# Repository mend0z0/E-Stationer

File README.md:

## Latest update

``
Working on the scheduling, hardware design, correcting diagrams, and...
``

# E-Stationer

E-Stationer is a project of consisting of two hardware parts, E-Pen and E-Paper, and 1 software parts that allow the user
to draw, write, read, and any sort of activities that you are able to do with a typical pen and paper.

## Features

- 
- 
- 

## Tech Stack

### Hardware

- **MCU:** 8bit PIC

- **Connection:** USB, UART, SPI, ADC, GPIO

- **PCB Layers:** 2Layers (None-controlled Impedance)

- **CAD:** KiCAD

### Firmware

- **OS:** State-machine

- **Programming Language:** C

- **IDE:** MPLABX IDE

### Application

- **Application:** Qt6

## WBS Chart

## Block Diagrams

## Screenshots

### Hardware

#### 3D_View

#### Assembled Hardware

### Application

## Demo

Insert gif or link to demo, it'll be my youtube channel

## LOGO

## Author

- [@Siavash Taher Parvar](https://www.linkedin.com/in/mend0z0)

## Support

[Support Link](https://github.com/sponsors/mend0z0)

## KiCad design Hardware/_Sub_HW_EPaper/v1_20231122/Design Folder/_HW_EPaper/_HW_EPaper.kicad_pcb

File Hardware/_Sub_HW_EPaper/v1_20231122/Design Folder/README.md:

# TODO list

A brief description of this todo list belongs to what project

## Tasks

- #### MUST to DO :
    - Adding 3D part to the 8-SOIC footprint for serial flash
    -
    - 
- #### Important :
    - List the works that efficient and optimized functionality of project depends on these tasks
    -
    - 
- #### General :
    - List tasks that are good to be done but the functionality of project doesn't depend on these
    -
    -

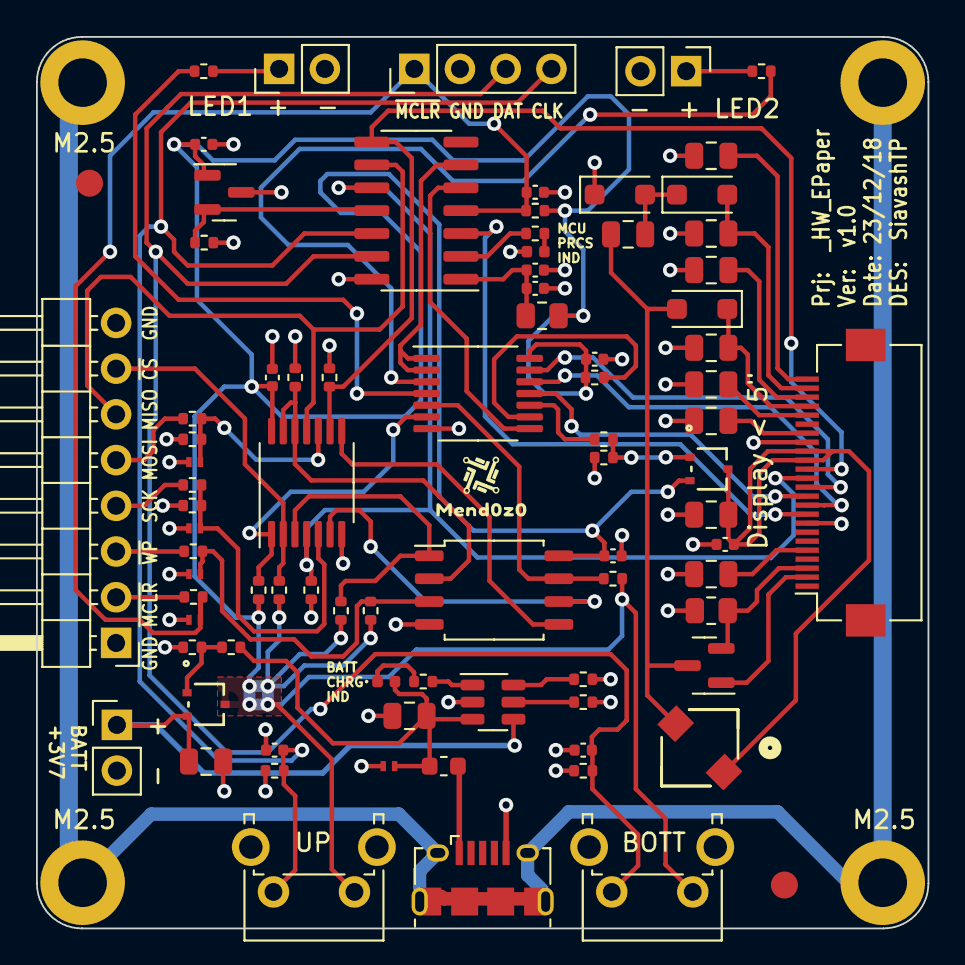
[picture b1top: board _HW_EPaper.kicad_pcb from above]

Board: 2 copper layers, 49.5 x 49.5 mm, 89 parts (0 on the bottom side), 60 nets.

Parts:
C301, C303, C703: 100nF_50V; C_0402_1005Metric
C302, C401, C501, C601, C801, C802, C901: 1uF_10V_X7R; C_0402_1005Metric
C701, C702, C704, C705, C706, C707, C708, C709, C710, C1001, C1002: 4u7F_16V; C_0805_2012Metric
D501, D502, D503, D504, D1001: TVS_6.5V_3A; CR_7PCT_L3F_TOS
D701, D702, D703: SS2040FL; D_SOD-123F
F1001: 100mA_15V_0.5R; Fuse_0603_1608Metric
FD1201, FD1202: 1.5mmX3mm; Fiducial_1.5mm_Mask3mm
GR1201: Mend0z0 Logo; LOGO_MEND0Z0
J301: HDR_4POS_VERT; PinHeader_1x04_P2.54mm_Vertical
J501: HDR_8POS_RA; PinHeader_1x08_P2.54mm_Horizontal
J701: FPC_24POS_BOTTOM_0.5P; Hirose_FH12-24S-0.5SH_1x24-1MP_P0.50mm_Horizontal
J1001: USB_microB_RA; USB_Micro-B_Amphenol_10118194_Horizontal
J1002, J1101, J1102: HDR_2POS_VERT; PinHeader_1x02_P2.54mm_Vertical
L701: 10uH_600mA; IND_CDRH3D11HPNP-100NC_SUM
LED301, LED1001: RED_2V; LED_0402_1005Metric
MH1201, MH1202, MH1203, MH1204: M2.5_DIN965; MountingHole_2.7mm_M2.5_DIN965_Pad
Q701: AS3400; SOT-23
Q702, Q1001: SSM3J117TU,LF; UFM_TOS
R301, R401, R402, R403, R501, R502, R505, R506, R507, R508, R509, R601, R703, R801, R802, R901, R1003, R1005: 10kR_1/16W_1%; R_0402_1005Metric
R302, R702, R1004: 470R_1/16W_1%; R_0402_1005Metric
R303: 1R_1/4W_1%; R_0805_2012Metric
R503, R504, R510, R511: 27R_1/16W_1%; R_0402_1005Metric
R701: 0.47R_1/8W_5%; R_0805_2012Metric
R1001, R1101, R1102: 100R_1/10W_1%; R_0402_1005Metric
R1002: 30kR_1/16W_1%; R_0402_1005Metric
SW801, SW802: SPST-NO; SW_Tactile_SPST_Angled_PTS645Vx31-2LFS
U301: PIC16F15223_8BIT; SO-14_3.9x8.65mm_P1.27mm
U401: W25Q64JVSSIQ; SOIC-8_5.275x5.275mm_P1.27mm
U501: SN74HCS32PWR; TSSOP-14_4.4x5mm_P0.65mm
U601: 74VHC164FT; TSSOP-14_4.4x5mm_P0.65mm
U901: MCP9700T-E/TT; SOT-23
U1001: RT9526AGE; SOT-23-6

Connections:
/BLOCK DIAGRAM/BATTERY CHARGER/RT_BATT: C1001.1, J1002.1, Q1001.2, U1001.4 (BATT)
/BLOCK DIAGRAM/BATTERY CHARGER/RT_CHG_SB: R1001.2, U1001.1 (CHG_SB)
/BLOCK DIAGRAM/BATTERY CHARGER/RT_IMIN: R1003.1, U1001.6 (IMIN)
/BLOCK DIAGRAM/BATTERY CHARGER/RT_ISET: R1002.1, U1001.5 (ISET)
/BLOCK DIAGRAM/BATTERY CHARGER/VBUS: C1002.1, D1001.1, F1001.2, LED1001.2, R1004.1, U1001.3 (VIN)
/BLOCK DIAGRAM/BATTERY CHARGER/V_BATT: C401.1, C501.1, C601.1, C901.1, Q702.2, Q1001.3, R301.1, R303.1, R401.1, R402.1, R403.1, R501.1, R502.1, R601.1, SW801.1, SW802.1, U401.8 (VCC), U501.14 (VCC), U601.14 (VCC), U901.1 (VDD)
/BLOCK DIAGRAM/DISPLAY DRIVER/E24_BUSY: J701.9, U301.3 (RA4)
/BLOCK DIAGRAM/DISPLAY DRIVER/E24_DC: J701.11, U601.11 (QF)
/BLOCK DIAGRAM/DISPLAY DRIVER/E24_GDR: J701.2, Q701.1
/BLOCK DIAGRAM/DISPLAY DRIVER/E24_RESE: J701.3, Q701.2, R701.1
/BLOCK DIAGRAM/DISPLAY DRIVER/E24_RST: J701.10, U601.12 (QG)
/BLOCK DIAGRAM/DISPLAY DRIVER/E24_VCOM: C709.1, J701.24
/BLOCK DIAGRAM/DISPLAY DRIVER/E24_VDD: C704.1, J701.18
/BLOCK DIAGRAM/DISPLAY DRIVER/E24_VDH: C706.1, J701.20
/BLOCK DIAGRAM/DISPLAY DRIVER/E24_VDHR: C701.1, J701.5
/BLOCK DIAGRAM/DISPLAY DRIVER/E24_VDL: C707.1, J701.22
/BLOCK DIAGRAM/DISPLAY DRIVER/E24_VGH: C705.1, D701.1, J701.21
/BLOCK DIAGRAM/DISPLAY DRIVER/E24_VGL: C710.1, D702.2, J701.23
/BLOCK DIAGRAM/DISPLAY DRIVER/E24_~CS: J701.12, U601.13 (QH)
/BLOCK DIAGRAM/DISPLAY DRIVER/PWR: R702.1, U601.10 (QE)
/BLOCK DIAGRAM/DISPLAY DRIVER/SPI_CLK: J701.13, R506.1, U301.10 (RC0), U501.4 (2A)
/BLOCK DIAGRAM/DISPLAY DRIVER/SPI_SDO: J701.14, R509.1, U301.8 (RC2), U501.9 (3A)
/BLOCK DIAGRAM/INPUT CIRCUIT/EXTERNAL_EEPROM_~WP: J501.3, R510.1
/BLOCK DIAGRAM/INPUT CIRCUIT/EXTERNAL_MCU_~MCLR: J501.2, R511.1
/BLOCK DIAGRAM/INPUT CIRCUIT/EXTERNAL_SPI_MISO: J501.6, U301.9 (RC1), U501.11 (4Y)
/BLOCK DIAGRAM/INPUT CIRCUIT/EXTERNAL_SPI_MOSI: J501.5, R504.1
/BLOCK DIAGRAM/INPUT CIRCUIT/EXTERNAL_SPI_SCK: J501.4, R503.1
/BLOCK DIAGRAM/INPUT CIRCUIT/EXTERNAL_SPI_~CS: J501.7, R501.2, U501.2 (1B)
/BLOCK DIAGRAM/INPUT CIRCUIT/MCU_SPI_~CS: R502.2, U501.1 (1A), U601.6 (QD)
/BLOCK DIAGRAM/INPUT CIRCUIT/SF_CLK: U401.6 (CLK), U501.6 (2Y)
/BLOCK DIAGRAM/INPUT CIRCUIT/SF_DI: U401.5 (DI), U501.8 (3Y)
/BLOCK DIAGRAM/INPUT CIRCUIT/SF_DO: R507.1, U401.2 (DO), U501.12 (4A), U501.13 (4B)
/BLOCK DIAGRAM/INPUT CIRCUIT/SF_~CS: R401.2, U401.1 (~CS), U501.3 (1Y)
/BLOCK DIAGRAM/INPUT CIRCUIT/SF_~WP: D503.1, R402.2, R510.2, U401.3 (~WP)
/BLOCK DIAGRAM/LED DRIVER/LED_1: R1101.1, U601.4 (QB)
/BLOCK DIAGRAM/LED DRIVER/LED_2: R1102.1, U601.3 (QA)
/BLOCK DIAGRAM/MICROCONTROLLER/IND_LED: R302.1, U301.2 (RA5)
/BLOCK DIAGRAM/MICROCONTROLLER/PIC_ICSPCLK: C802.1, J301.4, R802.1, SW802.2, U301.12 (ICSPCLK/RA1)
/BLOCK DIAGRAM/MICROCONTROLLER/PIC_ICSPDAT: C801.1, J301.3, R801.1, SW801.2, U301.13 (ICSPDAT/RA0)
/BLOCK DIAGRAM/MICROCONTROLLER/PIC_~MCLR: C301.1, D504.1, J301.1, R301.2, R511.2, U301.4 (~MCLR/RA3)
/BLOCK DIAGRAM/MICROCONTROLLER/SIPO_CLK: U301.5 (RC5), U601.8 (CK)
/BLOCK DIAGRAM/MICROCONTROLLER/SIPO_DATA: U301.6 (RC4), U601.1 (A), U601.2 (B)
/BLOCK DIAGRAM/MICROCONTROLLER/TEMP_ADC: R901.1, U301.11 (RA2), U901.2 (VOUT)
/BLOCK DIAGRAM/SERIAL FLASH/SF_~HOLD: R403.2, U401.7 (~HOLD), U601.5 (QC)
/BLOCK DIAGRAM/SHIFT REGISTER (SIPO)/74VHC164_~CLR: R601.2, U601.9 (~CLR)
Earth: J1001.6 (SH), MH1201.1, MH1202.1, MH1203.1, MH1204.1
GND: C301.2, C302.2, C303.2, C401.2, C501.2, C601.2, C701.2, C702.2, C703.2, C704.2, C705.2, C706.2, C707.2, C709.2, C710.2, C801.2, C802.2, C901.2, C1001.2, C1002.2, D501.2, D502.2, D503.2, D504.2, D703.1, D1001.2, J301.2, J501.1, J501.8, J701.8, J701.17, J1001.5 (GND), J1002.2, J1101.2, J1102.2, LED301.1, R505.2, R506.2, R507.2, R508.2, R509.2, R701.2, R703.2, R801.2, R802.2, R901.2, R1002.2, R1003.2, R1005.2, U301.14 (VSS), U401.4 (GND), U501.7 (GND), U601.7 (GND), U901.3 (GND), U1001.2 (GND)
unnamed: C702.1, C703.1, J701.15, J701.16, L701.1, Q702.3
unnamed: C708.1, D701.2, L701.2, Q701.3
unnamed: C708.2, D702.1, D703.2
unnamed: F1001.1, J1001.1 (VBUS)
unnamed: J1101.1, R1101.2
unnamed: J1102.1, R1102.2
unnamed: LED301.2, R302.2
unnamed: LED1001.1, R1001.1
unnamed: Q702.1, R702.2, R703.1
unnamed: Q1001.1, R1004.2, R1005.1
unnamed: C302.1, C303.1, R303.2, U301.1 (VDD)
unnamed: D501.1, R503.2, R505.1, U501.5 (2B)
unnamed: D502.1, R504.2, R508.1, U501.10 (3B)

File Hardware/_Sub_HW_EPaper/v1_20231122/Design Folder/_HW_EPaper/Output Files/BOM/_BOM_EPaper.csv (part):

"null","Sourced","Placed","References","Value","Footprint","Link","Description","Manufacturer","Part Number (Manufacturer)","Part Number (Vendor)","Vendor","Quantity"
1,"","","C701, C702, C704, C705, C706, C707, C708, C709, C710, C1001, C1002","4u7F_16V","C_0805_2012Metric","https://www.digikey.ca/en/products/detail/murata-electronics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","4.7 µF ±10% 16V Ceramic Capacitor X7R 0805 (2012 Metric)","Murata Electronics","GRM21BR71C475KE51L","490-14466-2-ND","Digikey",11
2,"","","C302, C401, C501, C601, C801, C802, C901","1uF_10V_X7R","C_0402_1005Metric","https://www.digikey.ca/en/products/detail/murata-electronics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","1 µF ±10% 10V Ceramic Capacitor X7R 0402 (1005 Metric)","Murata Electronics","GRM155Z71A105KE01D","490-GRM155Z71A105KE01DTR-ND","Digikey",7
3,"","","C301, C303, C703","100nF_50V","C_0402_1005Metric","https://www.digikey.ca/en/products/detail/murata-electronics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","0.1 µF ±10% 50V Ceramic Capacitor X7R 0402 (1005 Metric)","Murata Electronics","GRM155R71H104KE14J","490-13342-2-ND","Digikey",3
4,"","","R301, R401, R402, R403, R501, R502, R505, R506, R507, R508, R509, R601, R703, R801, R802, R901, R1003, R1005","10kR_1/16W_1%","R_0402_1005Metric","https://www.digikey.ca/en/products/detail/bourns-inc/CR0402-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","10 kOhms ±1% 0.063W, 1/16W Chip Resistor 0402 (1005 Metric) Thick Film","Bourns Inc.","CR0402-FX-1002GLF","CR0402-FX-1002GLFTR-ND","Digikey",18
5,"","","R503, R504, R510, R511","27R_1/16W_1%","R_0402_1005Metric","https://www.digikey.ca/en/products/detail/bourns-inc/CR0402-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","27 Ohms ±1% 0.063W, 1/16W Chip Resistor 0402 (1005 Metric) Thick Film","Bourns Inc.","CR0402-FX-27R0GLF","CR0402-FX-27R0GLFTR-ND","Digikey",4
6,"","","R302, R702, R1004","470R_1/16W_1%","R_0402_1005Metric","https://www.digikey.ca/en/products/detail/bourns-inc/CR0402-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","470 Ohms ±1% 0.063W, 1/16W Chip Resistor 0402 (1005 Metric) Thick Film","Bourns Inc.","CR0402-FX-4700GLF","CR0402-FX-4700GLFTR-ND","Digikey",3
7,"","","R1001, R1101, R1102","100R_1/10W_1%","R_0402_1005Metric","https://www.digikey.ca/en/products/detail/koa-speer-electron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","100 Ohms ±1% 0.1W, 1/10W Chip Resistor 0402 (1005 Metric) Automotive AEC-Q200, Moisture Resistant Thick Film","KOA Speer Electronics, Inc.","RK73H1ETTP1000F","2019-RK73H1ETTP1000FTR-ND","Digikey",3
8,"","","R303","1R_1/4W_1%","R_0805_2012Metric","https://www.digikey.ca/en/products/detail/stackpole-electron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","1 Ohms ±1% 0.25W, 1/4W Chip Resistor 0805 (2012 Metric) Anti-Sulfur Thin Film","Stackpole Electronics Inc","RNCP0805FTD1R00","RNCP0805FTD1R00TR-ND","Digikey",1
9,"","","R701","0.47R_1/8W_5%","R_0805_2012Metric","https://www.digikey.ca/en/products/detail/cts-resistor-produ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","470 mOhms ±5% 0.125W, 1/8W Chip Resistor 0805 (2012 Metric) Current Sense Thick Film","CTS Resistor Products","73L3R47J","73L3R47JTR-ND","Digikey",1
10,"","","R1002","30kR_1/16W_1%","R_0402_1005Metric","https://www.digikey.ca/en/products/detail/bourns-inc/CR0402-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","30 kOhms ±1% 0.063W, 1/16W Chip Resistor 0402 (1005 Metric) Thick Film","Bourns Inc.","CR0402-FX-3002GLF","CR0402-FX-3002GLFTR-ND","Digikey",1
11,"","","L701","10uH_600mA","IND_CDRH3D11HPNP-100NC_SUM","https://www.digikey.ca/en/products/detail/sumida-america-inc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","10 µH Shielded Inductor 600 mA 413mOhm Max Nonstandard","Sumida America Components Inc.","CDRH3D11HPNP-100NC","308-1966-2-ND","Digikey",1
12,"","","D501, D502, D503, D504, D1001","TVS_6.5V_3A","CR_7PCT_L3F_TOS","https://www.digikey.ca/en/products/detail/good-ark-semicondu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","20.5V Clamp 3A (8/20µs) Ipp Tvs Diode Surface Mount SOD-882","Good-Ark Semiconductor","GSEWT5B003","4786-GSEWT5B003TR-ND","Digikey",5
13,"","","D701, D702, D703","SS2040FL","D_SOD-123F","https://www.digikey.ca/en/products/detail/panjit-internation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","Diode 40 V 2A Surface Mount SOD-123FL","Panjit International Inc.","SS2040FL_R1_00001","3757-SS2040FL_R1_00001TR-ND","Digikey",3
14,"","","U301","PIC16F15223_8BIT","SO-14_3.9x8.65mm_P1.27mm","https://www.digikey.ca/en/products/detail/microchip-technolo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","PIC PIC® 16F, Functional Safety (FuSa) Microcontroller IC 8-Bit 32MHz 3.5KB (2K x 14) FLASH 14-SOIC","Microchip Technology","PIC16F15223-E/SL","150-PIC16F15223-E/SL-ND","Digikey",1
15,"","","U401","W25Q64JVSSIQ","SOIC-8_5.275x5.275mm_P1.27mm","https://www.digikey.ca/en/products/detail/winbond-electronic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","FLASH - NOR Memory IC 64Mbit SPI - Quad I/O 133 MHz 8-SOIC","Winbond Electronics","W25Q64JVSSIQ","W25Q64JVSSIQ-ND","Digikey",1
16,"","","U501","SN74HCS32PWR","TSSOP-14_4.4x5mm_P0.65mm","https://www.digikey.ca/en/products/detail/texas-instruments/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","OR Gate IC 4 Channel Schmitt Trigger Input 14-TSSOP","Texas Instruments","SN74HCS32PWR","296-SN74HCS32PWRTR-ND","Digikey",1
17,"","","U601","74VHC164FT","TSSOP-14_4.4x5mm_P0.65mm","https://www.digikey.ca/en/products/detail/toshiba-semiconduc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","Shift Shift Register 1 Element 8 Bit 14-TSSOP","Toshiba Semiconductor and Storage","74VHC164FT","264-74VHC164FTTR-ND","Digikey",1
18,"","","U901","MCP9700T-E/TT","SOT-23","https://www.digikey.ca/en/products/detail/microchip-technolo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","Temperature Sensor Analog, Local -40°C ~ 125°C 10mV/°C SOT-23-3","Microchip Technology","MCP9700T-E/TT","MCP9700T-E/TTTR-ND","Digikey",1
19,"","","U1001","RT9526AGE","SOT-23-6","https://www.digikey.ca/en/products/detail/richtek-usa-inc/RT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","Charger IC Lithium Ion SOT-23-6","Richtek USA Inc.","RT9526AGE","1028-1359-2-ND","Digikey",1
20,"","","F1001","100mA_15V_0.5R","Fuse_0603_1608Metric","https://www.digikey.ca/en/products/detail/eaton-electronics-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","PTC Resettable Fuse 15V 100 mA Ih Surface Mount 0603 (1608 Metric), Concave","Eaton - Electronics Division","PTS060315V010","283-PTS060315V010TR-ND","Digikey",1
21,"","","SW801, SW802","SPST-NO","SW_Tactile_SPST_Angled_PTS645Vx31-2LFS","https://www.digikey.ca/en/products/detail/c-k/PTS645VH31-2-L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","Tactile Switch SPST-NO Side Actuated Through Hole, Right Angle","C&K","PTS645VH31-2 LFS","CKN9118-ND","Digikey",2
22,"","","LED301, LED1001","RED_2V","LED_0402_1005Metric","https://www.digikey.ca/en/products/detail/harvatek-corporati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","Red 624nm LED Indication - Discrete 2V 0402 (1005 Metric)","Harvatek Corporation","B2841USD-20D001014U1930","3147-B2841USD-20D001014U1930TR-ND","Digikey",2
23,"","","Q702, Q1001","SSM3J117TU,LF","UFM_TOS","https://www.digikey.ca/en/products/detail/toshiba-semiconduc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","P-Channel 30 V 2A (Ta) 500mW (Ta) Surface Mount UFM","Toshiba Semiconductor and Storage","SSM3J117TU,LF","SSM3J117TULFTR-ND","Digikey",2
24,"","","Q701","AS3400","SOT-23","https://www.digikey.ca/en/products/detail/anbon-semiconducto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","N-Channel 30 V 5.6A (Ta) 1.2W (Ta) Surface Mount SOT-23","ANBON SEMICONDUCTOR (INT'L) LIMITED","AS3400","4530-AS3400TR-ND","Digikey",1
25,"","","J1002, J1101, J1102","HDR_2POS_VERT","PinHeader_1x02_P2.54mm_Vertical","https://www.digikey.ca/en/products/detail/adam-tech/PH1-02-U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","Connector Header Through Hole 2 position 0.100"" (2.54mm)","Adam Tech","PH1-02-UA","2057-PH1-02-UA-ND","Digikey",3
26,"","","J301","HDR_4POS_VERT","PinHeader_1x04_P2.54mm_Vertical","https://www.digikey.ca/en/products/detail/adam-tech/PH1-04-U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","Connector Header Through Hole 4 position 0.100"" (2.54mm)","Adam Tech","PH1-04-UA","2057-PH1-04-UA-ND","Digikey",1
27,"","","J501","HDR_8POS_RA","PinHeader_1x08_P2.54mm_Horizontal","https://www.digikey.ca/en/products/detail/adam-tech/PH1RB-08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","Connector Header Through Hole, Right Angle 8 position 0.100"" (2.54mm)","Adam Tech","PH1RB-08-UA","2057-PH1RB-08-UA-ND","Digikey",1
28,"","","J701","FPC_24POS_BOTTOM_0.5P","Hirose_FH12-24S-0.5SH_1x24-1MP_P0.50mm_Horizontal","https://www.digikey.ca/en/products/detail/cvilux-usa/CF35242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","24 Position FFC, FPC Connector Contacts, Bottom 0.020"" (0.50mm) Surface Mount, Right Angle","Cvilux USA","CF35242D0RD-NH","2987-CF35242D0RD-NHTR-ND","Digikey",1
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
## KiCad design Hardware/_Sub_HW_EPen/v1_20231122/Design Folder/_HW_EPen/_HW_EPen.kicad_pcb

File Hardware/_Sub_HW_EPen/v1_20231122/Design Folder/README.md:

# TODO list

This todo list belongs to _SUB_HW_EPen, the hardware part of EPen sub project. 

## Tasks

- #### MUST to DO :
    - Writing the LED indicator status once it's been determined how it should blink based on different situation.
    - Adding proper screw component and link in mechanical page
    - Adding a good enclosure 
	- Adding the PCB and it's size to mechanical page
	- Adding 3D model for USB footprint (P/N: 10118194-0001LF) 
- #### Important :
    - List the works that efficient and optimized functionality of project depends on these tasks
    -
    - 
- #### General :
    - List tasks that are good to be done but the functionality of project doesn't depend on these
    -
    -

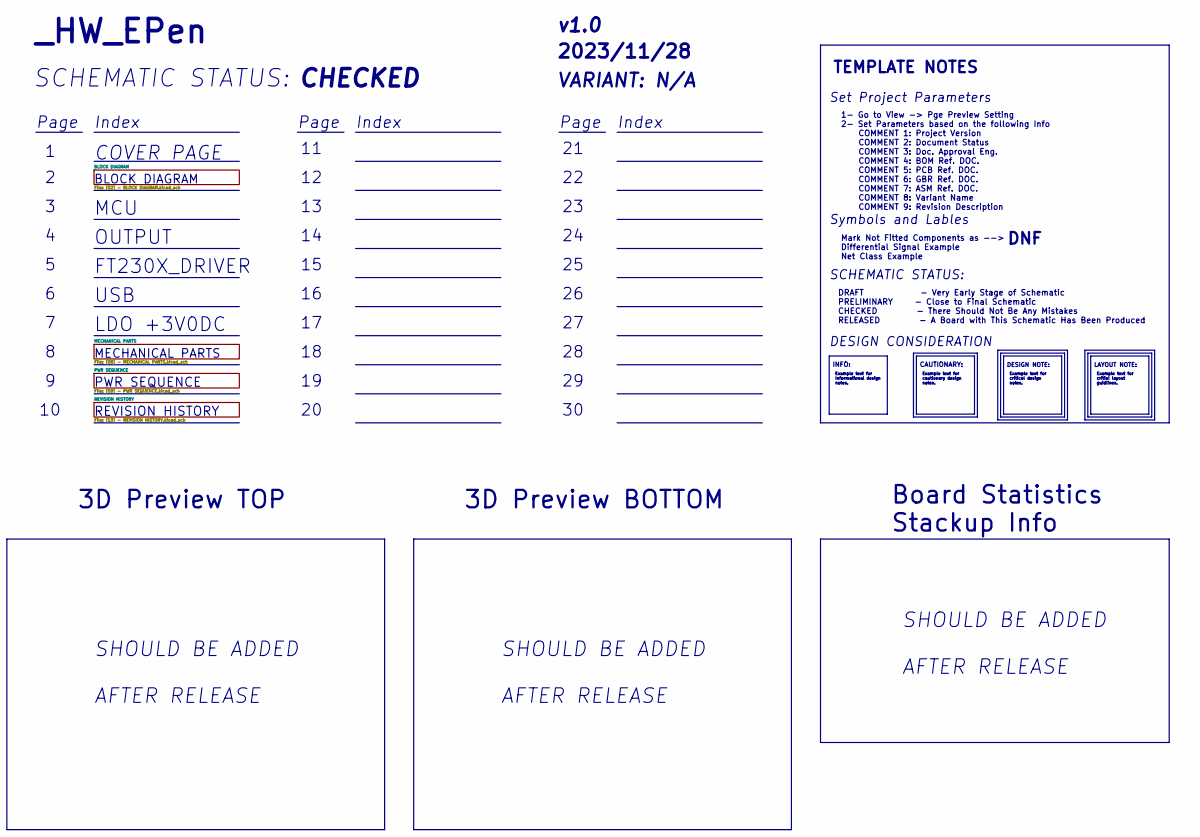
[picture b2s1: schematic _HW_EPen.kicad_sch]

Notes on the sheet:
Set Project Parameters
SHOULD BE ADDED AFTER RELEASE
MECHANICAL PARTS
Index
SCHEMATIC STATUS:
SCHEMATIC STATUS:
Page
DESIGN CONSIDERATION
USB
Example text for Informational design notes.
${COMMENT2}
${REVISION}
VARIANT: ${COMMENT8}
1- Go to View -> Pge Preview Setting 2- Set Parameters based on the following Info COMMENT 1: Project Version COMMENT 2: Document Status COMMENT 3: Doc. Approval Eng. COMMENT 4: BOM Ref. DOC. COMMENT 5: PCB Ref. DOC. COMMENT 6: GBR Ref. DOC. COMMENT 7: ASM Ref. DOC. COMMENT 8: Variant Name COMMENT 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
COVER PAGE
OUTPUT
Mark Not Fitted Components as --> Differential Signal Example Net Class Example
Board Statistics Stackup Info
TEMPLATE NOTES
${ISSUE_DATE}
Example text for critial layout guidlines.
MCU
INFO:
${TITLE}
DESIGN NOTE:
Example text for critical design notes.
3D Preview TOP
PWR SEQUENCE
3D Preview BOTTOM
Example text for cautionary design notes.
CAUTIONARY:
Symbols and Lables
DNF
LDO +3V0DC
REVISION HISTORY
FT230X_DRIVER
BLOCK DIAGRAM
LAYOUT NOTE:
DRAFT - Very Early Stage of Schematic PRELIMINARY - Close to Final Schematic CHECKED - There Should Not Be Any Mistakes RELEASED - A Board with This Schematic Has Been Produced

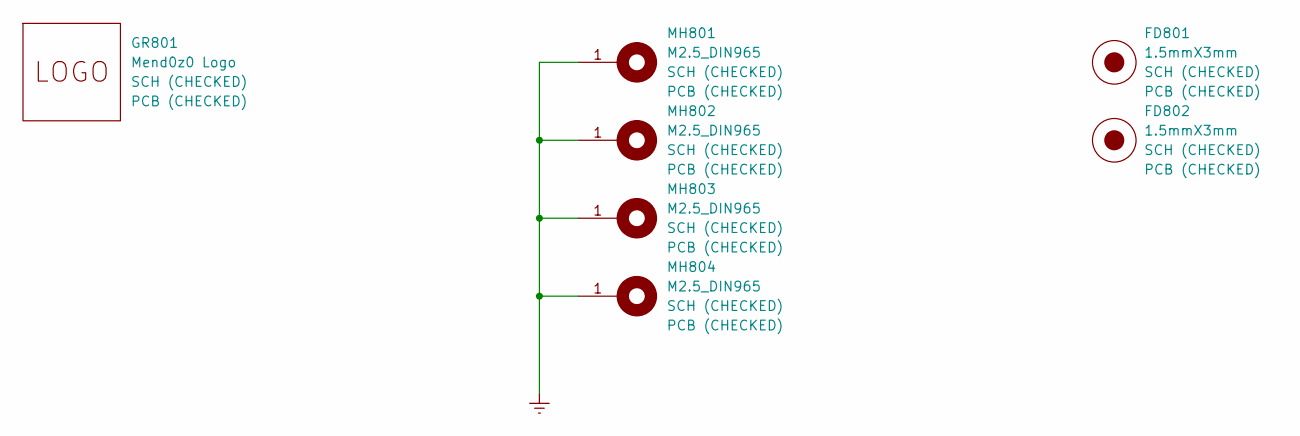
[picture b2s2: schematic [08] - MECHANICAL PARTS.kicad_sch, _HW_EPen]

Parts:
FD801, FD802: 1.5mmX3mm; Fiducial_1.5mm_Mask3mm
GR801: Mend0z0 Logo; LOGO_MEND0Z0
MH801, MH802, MH803, MH804: M2.5_DIN965; MountingHole_2.7mm_M2.5_DIN965_Pad

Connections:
Earth: MH801.1, MH802.1, MH803.1, MH804.1; also elsewhere on the board

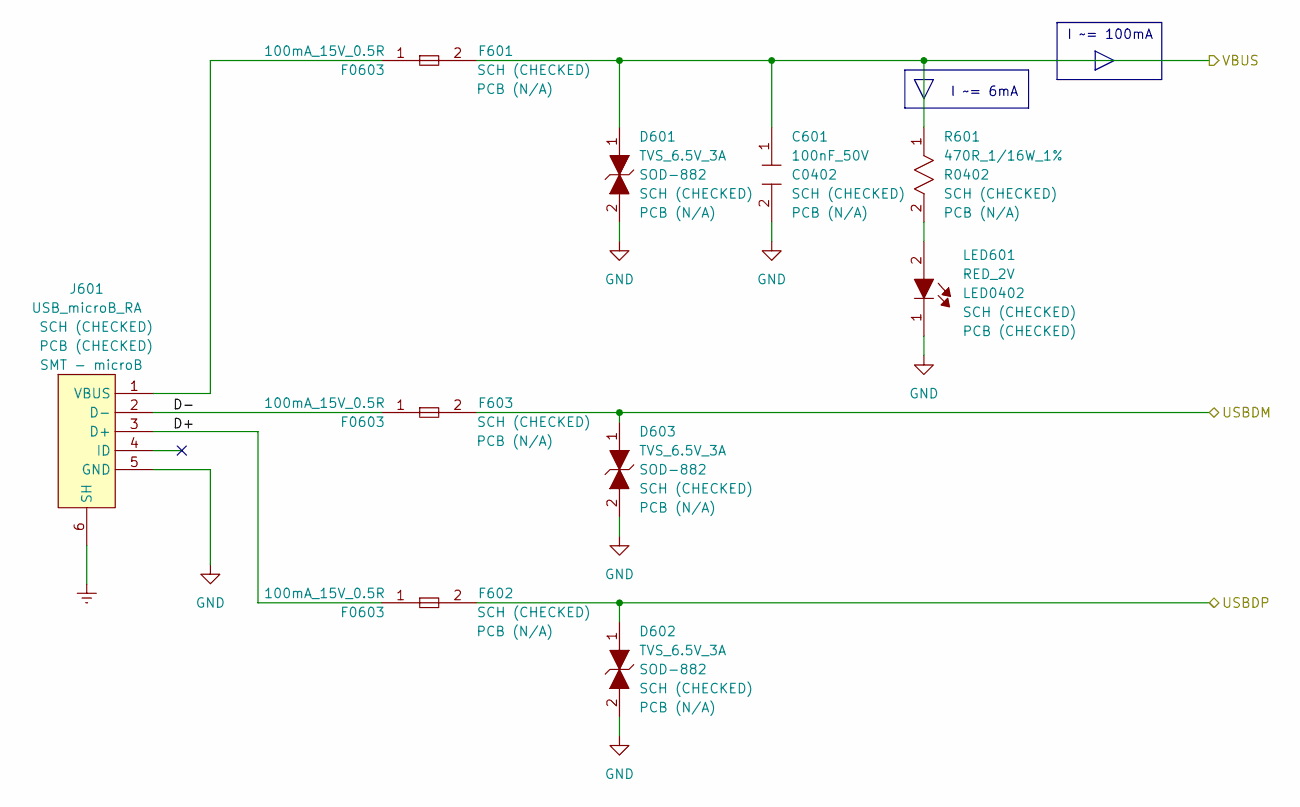
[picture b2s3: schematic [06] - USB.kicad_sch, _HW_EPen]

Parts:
C601: 100nF_50V; C_0402_1005Metric; Part Number (Manufactur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 GRM155R71H104KE14J
D601, D602, D603: TVS_6.5V_3A; CR_7PCT_L3F_TOS; Part Number (Vendor) 4786-GSEWT5B003TR-ND
F601, F602, F603: 100mA_15V_0.5R; Fuse_0603_1608Metric; Part Number (Vendor) 283-PTS060315V010TR-ND
J601: USB_microB_RA; USB_Micro-B_Amphenol_10118194_Horizontal; Part Number (Vendor) 609-4618-2-ND
LED601: RED_2V; LED_0402_1005Metric; Part Number (Vendor) 3147-B2841USD-20D001014U1930TR-ND
R601: 470R_1/16W_1%; R_0402_1005Metric; Part Number (Vendor) CR0402-FX-4700GLFTR-ND

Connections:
/BLOCK DIAGRAM/FT230X_DRIVER/USBDM: D603.1, F603.2; also elsewhere on the board
/BLOCK DIAGRAM/FT230X_DRIVER/USBDP: D602.1, F602.2; also elsewhere on the board
/BLOCK DIAGRAM/LDO +3V0DC/+5VDC: C601.1, D601.1, F601.2, R601.1; also elsewhere on the board
/BLOCK DIAGRAM/USB/D+: F602.1, J601.3 (D+)
/BLOCK DIAGRAM/USB/D-: F603.1, J601.2 (D-)
Earth: J601.6 (SH); also elsewhere on the board
GND: C601.2, D601.2, D602.2, D603.2, J601.5 (GND), LED601.1; also elsewhere on the board
unnamed: F601.1, J601.1 (VBUS)
unnamed: LED601.2, R601.2

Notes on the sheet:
I ~= 100mA
I ~= 6mA

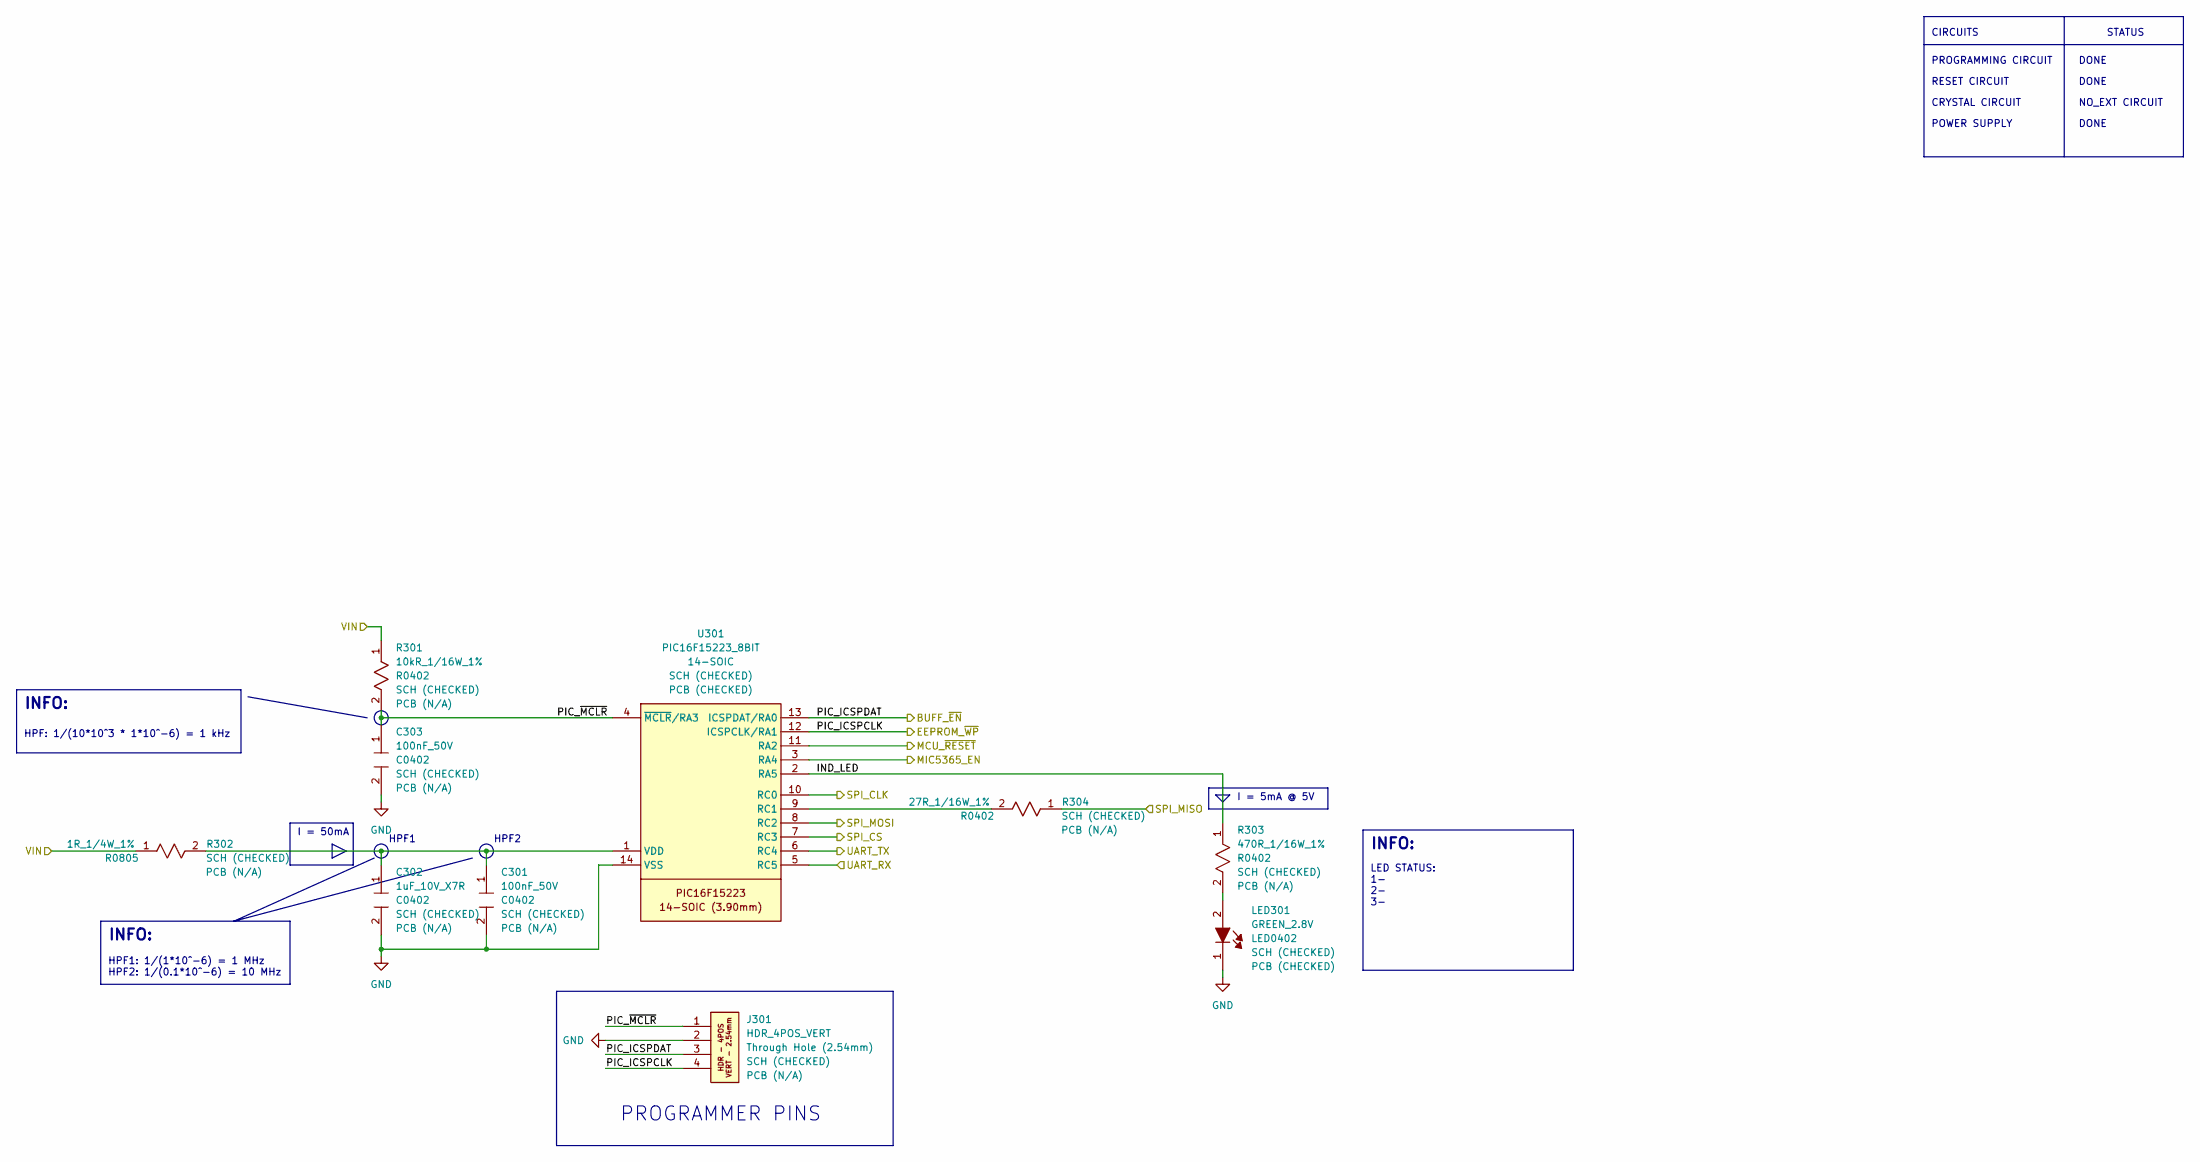
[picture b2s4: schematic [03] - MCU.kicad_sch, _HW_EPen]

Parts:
C301, C303: 100nF_50V; C_0402_1005Metric; Part Number (Manufactur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 GRM155R71H104KE14J
C302: 1uF_10V_X7R; C_0402_1005Metric; Part Number (Vendor) 490-GRM155Z71A105KE01DTR-ND
J301: HDR_4POS_VERT; PinHeader_1x04_P2.54mm_Vertical; Part Number (Vendor) 2057-PH1-04-UA-ND
LED301: GREEN_2.8V; LED_0402_1005Metric; Part Number (Vendor) 3147-B2841NG--05D000514U1930TR-ND
R301: 10kR_1/16W_1%; R_0402_1005Metric; Part Number (Vendor) CR0402-FX-1002GLFTR-ND
R302: 1R_1/4W_1%; R_0805_2012Metric; Part Number (Vendor) RNCP0805FTD1R00TR-ND
R303: 470R_1/16W_1%; R_0402_1005Metric; Part Number (Vendor) CR0402-FX-4700GLFTR-ND
R304: 27R_1/16W_1%; R_0402_1005Metric; Part Number (Vendor) CR0402-FX-27R0GLFTR-ND
U301: PIC16F15223_8BIT; SO-14_3.9x8.65mm_P1.27mm; Part Number (Vendor) 150-PIC16F15223-E/SL-ND

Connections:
/BLOCK DIAGRAM/FT230X_DRIVER/UART_RX: U301.6 (RC4); also elsewhere on the board
/BLOCK DIAGRAM/FT230X_DRIVER/UART_TX: U301.5 (RC5); also elsewhere on the board
/BLOCK DIAGRAM/LDO +3V0DC/+5VDC: R301.1, R302.1; also elsewhere on the board
/BLOCK DIAGRAM/LDO +3V0DC/MIC5365_PIN_EN: U301.3 (RA4); also elsewhere on the board
/BLOCK DIAGRAM/MCU/IND_LED: R303.1, U301.2 (RA5)
/BLOCK DIAGRAM/MCU/MCU_~RESET: U301.11 (RA2); also elsewhere on the board
/BLOCK DIAGRAM/MCU/PIC_ICSPCLK: J301.4, U301.12 (ICSPCLK/RA1); also elsewhere on the board
/BLOCK DIAGRAM/MCU/PIC_ICSPDAT: J301.3, U301.13 (ICSPDAT/RA0); also elsewhere on the board
/BLOCK DIAGRAM/MCU/PIC_~MCLR: C303.1, J301.1, R301.2, U301.4 (~MCLR/RA3)
/BLOCK DIAGRAM/MCU/SPI_CLK: U301.10 (RC0); also elsewhere on the board
/BLOCK DIAGRAM/MCU/SPI_CS: U301.7 (RC3); also elsewhere on the board
/BLOCK DIAGRAM/MCU/SPI_MISO: R304.1; also elsewhere on the board
/BLOCK DIAGRAM/MCU/SPI_MOSI: U301.8 (RC2); also elsewhere on the board
GND: C301.2, C302.2, C303.2, J301.2, LED301.1, U301.14 (VSS); also elsewhere on the board
unnamed: LED301.2, R303.2
unnamed: R304.2, U301.9 (RC1)
unnamed: C301.1, C302.1, R302.2, U301.1 (VDD)

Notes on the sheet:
HPF: 1/(10*10^3 * 1*10^-6) = 1 kHz
INFO:
I = 50mA
DONE
I = 5mA @ 5V
CRYSTAL CIRCUIT
HPF2
PROGRAMMER PINS
STATUS
LED STATUS: 1- 2- 3-
HPF1
POWER SUPPLY
NO_EXT CIRCUIT
HPF1: 1/(1*10^-6) = 1 MHz HPF2: 1/(0.1*10^-6) = 10 MHz
PROGRAMMING CIRCUIT
CIRCUITS
RESET CIRCUIT

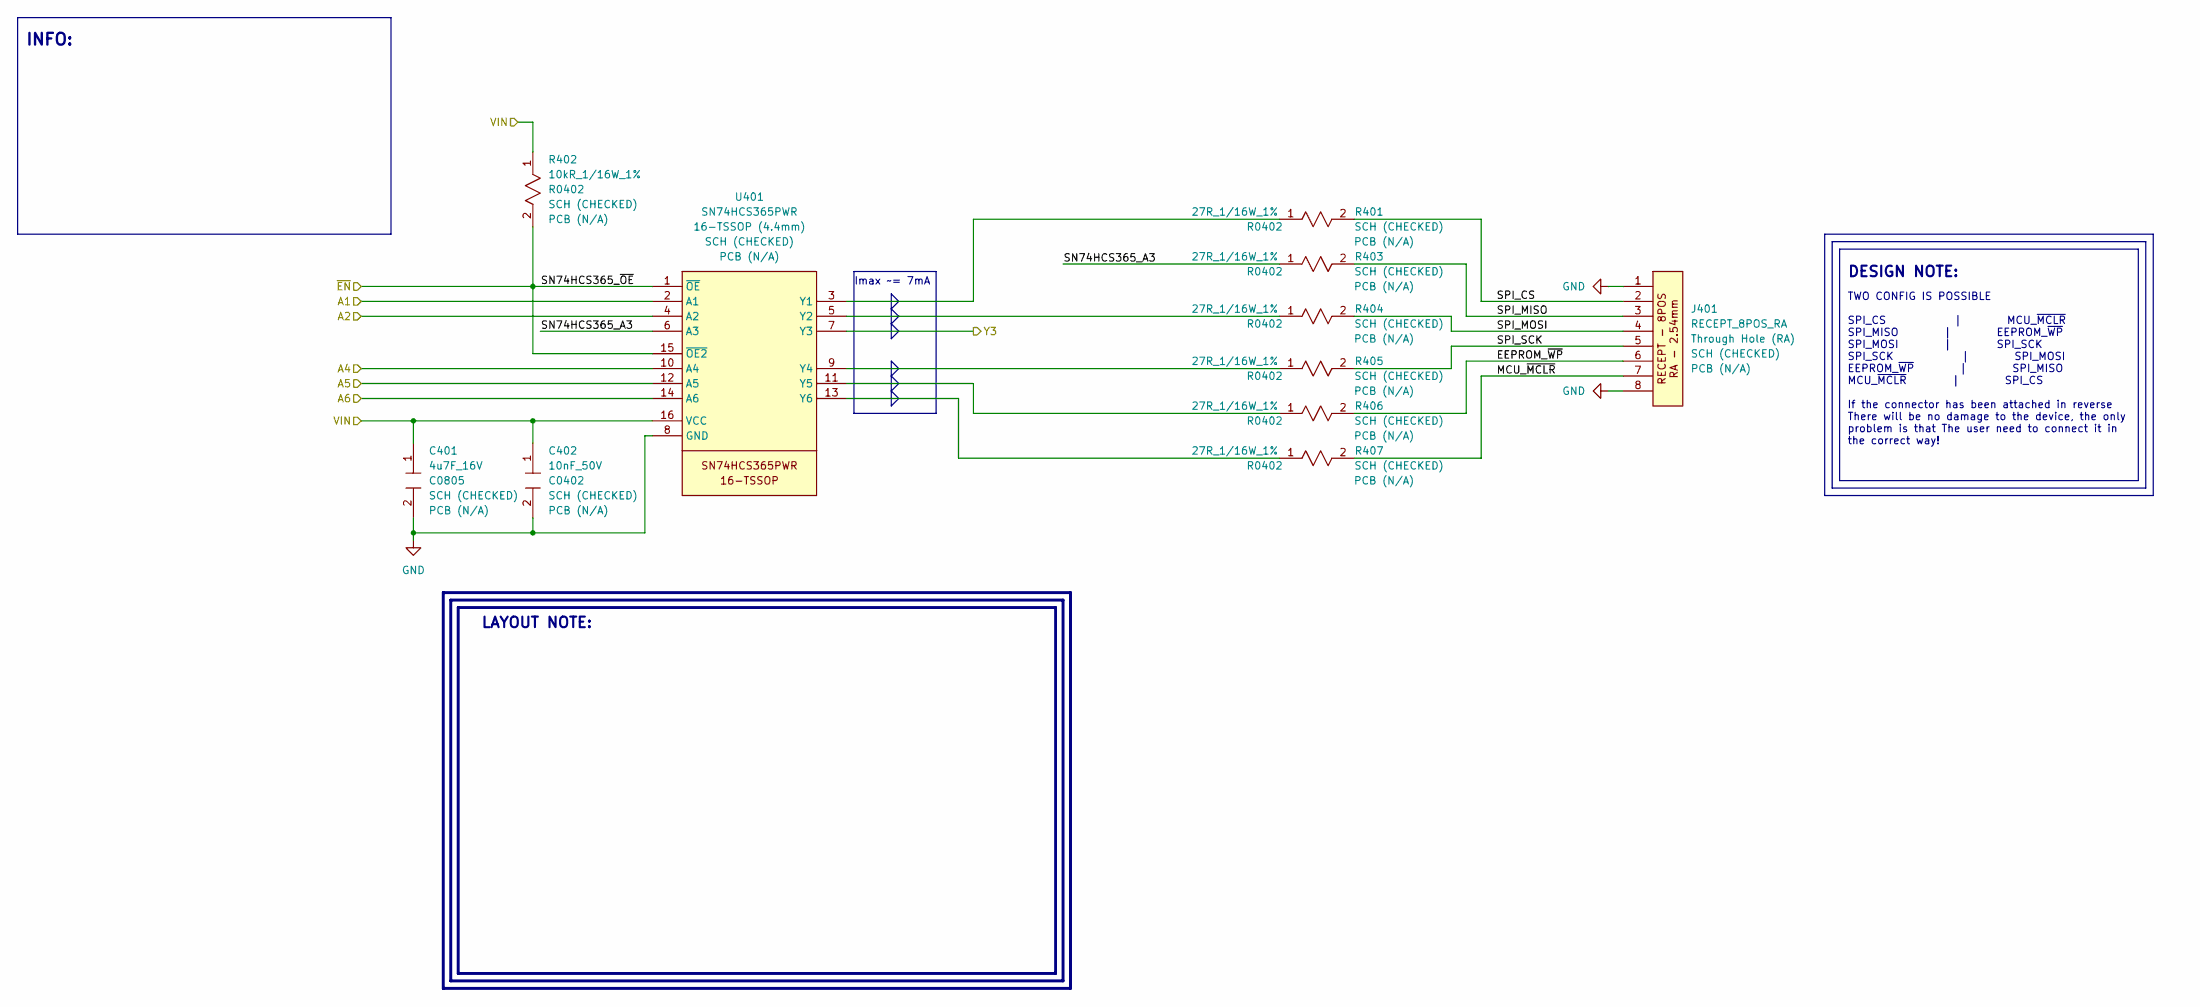
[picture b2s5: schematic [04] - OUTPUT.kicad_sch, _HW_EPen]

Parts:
C401: 4u7F_16V; C_0805_2012Metric; Part Number (Vendor) 490-14466-2-ND
C402: 10nF_50V; C_0402_1005Metric; Part Number (Vendor) 1276-1028-2-ND
J401: RECEPT_8POS_RA; PinSocket_1x08_P2.54mm_Horizontal; Part Number (Vendor) SAM1195-08-ND
R401, R403, R404, R405, R406, R407: 27R_1/16W_1%; R_0402_1005Metric; Part Number (Vendor) CR0402-FX-27R0GLFTR-ND
R402: 10kR_1/16W_1%; R_0402_1005Metric; Part Number (Vendor) CR0402-FX-1002GLFTR-ND
U401: SN74HCS365PWR; TSSOP-16_4.4x5mm_P0.65mm; Part Number (Vendor) 296-SN74HCS365PWRTR-ND

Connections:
/BLOCK DIAGRAM/LDO +3V0DC/+3VDC: C401.1, C402.1, R402.1, U401.16 (VCC); also elsewhere on the board
/BLOCK DIAGRAM/MCU/MCU_~RESET: U401.14 (A6); also elsewhere on the board
/BLOCK DIAGRAM/MCU/PIC_ICSPCLK: U401.12 (A5); also elsewhere on the board
/BLOCK DIAGRAM/MCU/PIC_ICSPDAT: R402.2, U401.1 (~OE), U401.15 (~OE2); also elsewhere on the board
/BLOCK DIAGRAM/MCU/SPI_CLK: U401.10 (A4); also elsewhere on the board
/BLOCK DIAGRAM/MCU/SPI_CS: U401.2 (A1); also elsewhere on the board
/BLOCK DIAGRAM/MCU/SPI_MISO: U401.7 (Y3); also elsewhere on the board
/BLOCK DIAGRAM/MCU/SPI_MOSI: U401.4 (A2); also elsewhere on the board
/BLOCK DIAGRAM/OUTPUT/EEPROM_~WP: J401.6, R406.2
/BLOCK DIAGRAM/OUTPUT/MCU_~MCLR: J401.7, R407.2
/BLOCK DIAGRAM/OUTPUT/SN74HCS365_A3: R403.1, U401.6 (A3)
/BLOCK DIAGRAM/OUTPUT/SPI_CS: J401.2, R401.2
/BLOCK DIAGRAM/OUTPUT/SPI_MISO: J401.3, R403.2
/BLOCK DIAGRAM/OUTPUT/SPI_MOSI: J401.4, R404.2
/BLOCK DIAGRAM/OUTPUT/SPI_SCK: J401.5, R405.2
GND: C401.2, C402.2, J401.1, J401.8, U401.8 (GND); also elsewhere on the board
unnamed: R401.1, U401.3 (Y1)
unnamed: R404.1, U401.5 (Y2)
unnamed: R405.1, U401.9 (Y4)
unnamed: R406.1, U401.11 (Y5)
unnamed: R407.1, U401.13 (Y6)

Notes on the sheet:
DESIGN NOTE:
TWO CONFIG IS POSSIBLE SPI_CS | MCU_~{MCLR} SPI_MISO | EEPROM_~{WP} SPI_MOSI | SPI_SCK SPI_SCK | SPI_MOSI EEPROM_~{WP} | SPI_MISO MCU_~{MCLR} | SPI_CS If the connector has been attached in reverse There will be no damage to the device, the only problem is that The user need to connect it in the cor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
INFO:
LAYOUT NOTE:
Imax ~= 7mA

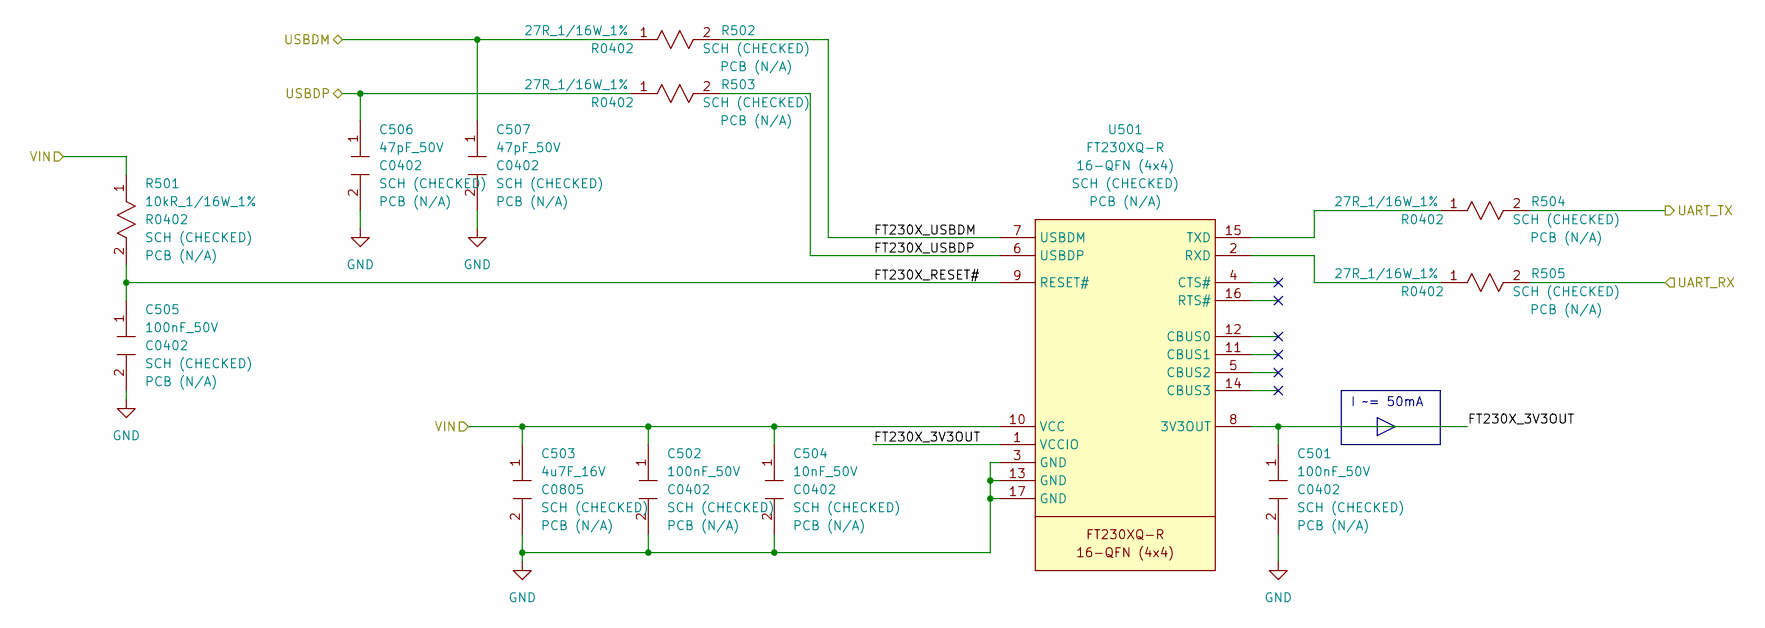
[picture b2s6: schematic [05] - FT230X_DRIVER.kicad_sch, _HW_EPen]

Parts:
C501, C502, C505: 100nF_50V; C_0402_1005Metric; Part Number (Manufactur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 GRM155R71H104KE14J
C503: 4u7F_16V; C_0805_2012Metric; Part Number (Vendor) 490-14466-2-ND
C504: 10nF_50V; C_0402_1005Metric; Part Number (Vendor) 1276-1028-2-ND
C506, C507: 47pF_50V; C_0402_1005Metric; Part Number (Vendor) 399-C0402C470J5RACAUTOTR-ND
R501: 10kR_1/16W_1%; R_0402_1005Metric; Part Number (Vendor) CR0402-FX-1002GLFTR-ND
R502, R503, R504, R505: 27R_1/16W_1%; R_0402_1005Metric; Part Number (Vendor) CR0402-FX-27R0GLFTR-ND
U501: FT230XQ-R; QFN-16-1EP_4x4mm_P0.65mm_EP2.1x2.1mm_ThermalVias; Part Number (Vendor) 768-1130-2-ND

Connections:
/BLOCK DIAGRAM/FT230X_DRIVER/FT230X_3V3OUT: C501.1, U501.1 (VCCIO), U501.8 (3V3OUT)
/BLOCK DIAGRAM/FT230X_DRIVER/FT230X_RESET#: C505.1, R501.2, U501.9 (RESET#)
/BLOCK DIAGRAM/FT230X_DRIVER/FT230X_USBDM: R502.2, U501.7 (USBDM)
/BLOCK DIAGRAM/FT230X_DRIVER/FT230X_USBDP: R503.2, U501.6 (USBDP)
/BLOCK DIAGRAM/FT230X_DRIVER/UART_RX: R505.2; also elsewhere on the board
/BLOCK DIAGRAM/FT230X_DRIVER/UART_TX: R504.2; also elsewhere on the board
/BLOCK DIAGRAM/FT230X_DRIVER/USBDM: C507.1, R502.1; also elsewhere on the board
/BLOCK DIAGRAM/FT230X_DRIVER/USBDP: C506.1, R503.1; also elsewhere on the board
/BLOCK DIAGRAM/LDO +3V0DC/+5VDC: C502.1, C503.1, C504.1, R501.1, U501.10 (VCC); also elsewhere on the board
GND: C501.2, C502.2, C503.2, C504.2, C505.2, C506.2, C507.2, U501.3 (GND), U501.13 (GND), U501.17 (GND); also elsewhere on the board
unnamed: R505.1, U501.2 (RXD)
unnamed: R504.1, U501.15 (TXD)

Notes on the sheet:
I ~= 50mA
